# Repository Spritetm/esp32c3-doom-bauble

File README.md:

Doom on an ESP32-C3 based Christmas tree bauble
===============================================

This uses the GBA Doom from https://github.com/doomhack/GBADoom to put Doom on a tiny Christmas
bauble. More information is on https://spritesmods.com/?art=doom-bauble .

Directories
-----------

- case: contains OpenSCAD case designs. 
- esp32c3-doom: Contains the firmware. This needs ESP-IDF 5.0 or higher to compile.
- pcb - KiCad PCB designs

Case
----

You should be able to print the case on a FDM ('hot plastic squirter'-type) machine, 
but it'll look better when printed on a SLA/LCD/DLP ('ultra-violet goo hardener'-type)
printer. I masked it with masking tape afterwards and painted it with model paint
(specifically Tamiya TS-81 and TS-06 rattle-can paint).

PCB
---
The PCB designs and schematics are in Kicad format. Look at the schematics for hints 
for components not on the BOM. Note that the 'headers' on the PCB are supposed to have
wires directly soldered to it; space doesn't really allow for actual headers.

Firmware
--------

To build this, you need esp-idf 5.0 or higher. (I used git commit 4c1ff6016a, for reference.) You
also need to make sure you have 8MiB or more flash on your ESP32C3. You can use the standard 
esp-idf building & flashing procedure ('idf.py flash'). Note that you also need to flash the Doom
WAD to the flash. The flash-doom-wad.sh shellscript gives an example on how to do that with the
included doom1gba.wad file; using this will give you the shareware version of Doom (which includes
all the levels of Episode 1).

It is possible to use a different Doom WAD as a basis for this, but you need to manually convert 
it first. Tools and information for that is in the esp32c3-doom/GbaWadUtil. Most importantly, you
probably want to convert any music to IMF format and re-record demos before running GbaWadUtil
to generate the final WAD to be flashed.

Note that this Doom version is not compatible with demos that are included in existing WAD files; 
while they will play, they will likely desync early on. As such, you may want to re-record the
demo files. There's a rudimentary setup for this in esp32c3-doom/main/sdl which can be used to
compile this version of Doom for SDL input and output. After that, you can edit d_main.c and
recompile to enable demo recording of one map.

Note on input devices
---------------------

The ESP32C3 will connect to any BT-LE device that supports HID and is set to pairing mode. 
BT Classic devices aren't supported nor detected. Do note that connecting to an input 
device is not fast. Wait about 10 seconds after putting a device into pairing mode before 
using it.

Joystick has been tested and seems to work OK (although the input is digital only, no analog
movement is supported)

Mouse works, but again: inputs get flattened to digital-only. You may need a mouse 
with >=3 buttons to start the game (mouse wheel press / middle button = start)

Keyboard is implemented but entirely untested. The keymapping should be: z and x for 
shoot & open, a and s for left and right strafe, tab for select, enter for start, cursor 
keys for movement.

In general: weapon selection is hold open + use the strafe keys.

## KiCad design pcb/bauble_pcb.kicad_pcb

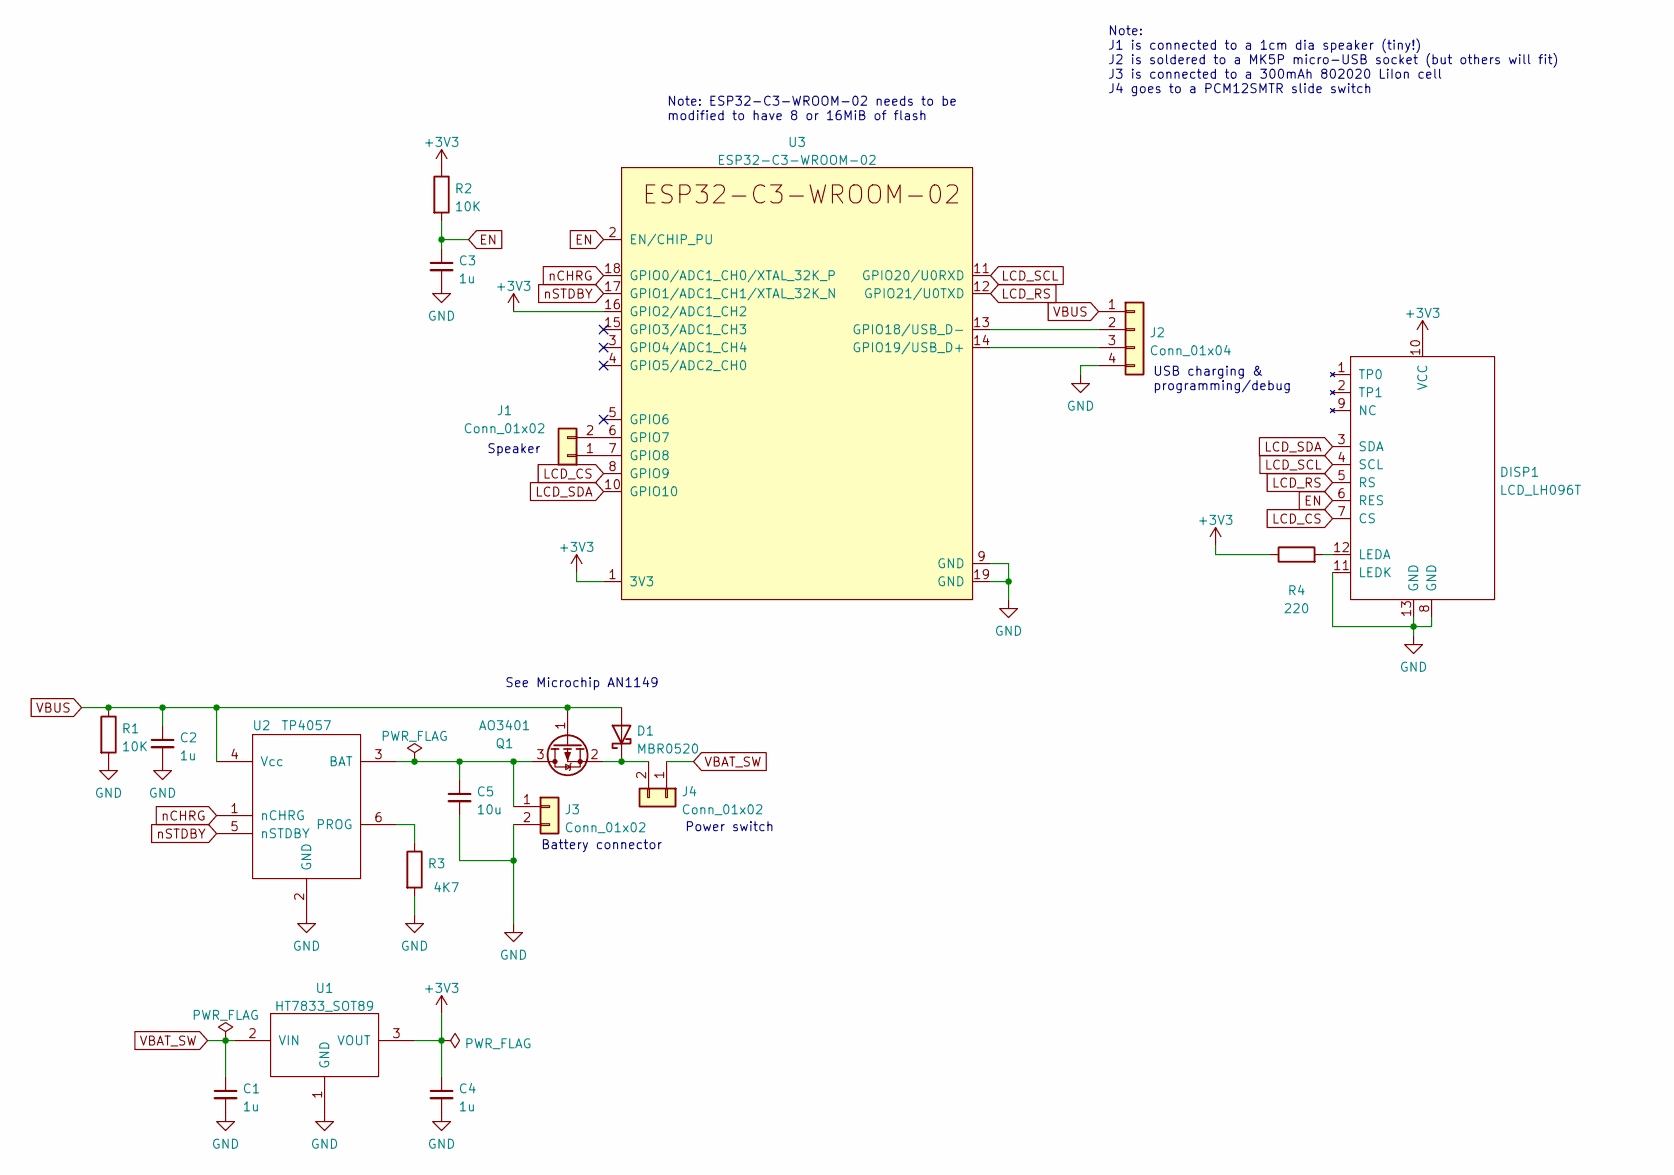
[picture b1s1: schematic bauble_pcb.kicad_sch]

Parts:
C1, C2, C3, C4: 1u; C_0603_1608Metric
C5: 10u; C_0805_2012Metric
D1: MBR0520; D_SOD-123
DISP1: LCD_LH096T; LCD_LH086T
J1, J3, J4: Conn_01x02; PinHeader_1x02_P1.27mm_Vertical
J2: Conn_01x04; PinHeader_1x04_P1.27mm_Vertical
Q1: AO3401; SOT-23
R1, R2: 10K; R_0603_1608Metric
R3: 4K7; R_0603_1608Metric
R4: 220; R_0603_1608Metric
U1: HT7833_SOT89; SOT-89-3
U2: TP4057; SOT-23-6
U3: ESP32-C3-WROOM-02

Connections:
+3V3: C4.1, DISP1.10 (VCC), R2.1, R4.1, U1.3 (VOUT), U3.1 (3V3), U3.16 (GPIO2/ADC1_CH2)
EN: C3.1, DISP1.6 (RES), R2.2, U3.2 (EN/CHIP_PU)
GND: C1.2, C2.2, C3.2, C4.2, C5.2, DISP1.8 (GND), DISP1.11 (LEDK), DISP1.13 (GND), J2.4, J3.2, R1.2, R3.2, U1.1 (GND), U2.2 (GND), U3.9 (GND), U3.19 (GND)
LCD_CS: DISP1.7 (CS), U3.8 (GPIO9)
LCD_RS: DISP1.5 (RS), U3.12 (GPIO21/U0TXD)
LCD_SCL: DISP1.4 (SCL), U3.11 (GPIO20/U0RXD)
LCD_SDA: DISP1.3 (SDA), U3.10 (GPIO10)
unnamed: C5.1, J3.1, Q1.3 (D), U2.3 (BAT)
unnamed: D1.1 (K), J4.2, Q1.2 (S)
unnamed: DISP1.12 (LEDA), R4.2
unnamed: J2.2, U3.13 (GPIO18/USB_D-)
unnamed: J2.3, U3.14 (GPIO19/USB_D+)
unnamed: R3.1, U2.6 (PROG)
unnamed: J1.2, U3.6 (GPIO7)
unnamed: J1.1, U3.7 (GPIO8)
VBAT_SW: C1.1, J4.1, U1.2 (VIN)
VBUS: C2.1, D1.2 (A), J2.1, Q1.1 (G), R1.1, U2.4 (Vcc)
nCHRG: U2.1 (nCHRG), U3.18 (GPIO0/ADC1_CH0/XTAL_32K_P)
nSTDBY: U2.5 (nSTDBY), U3.17 (GPIO1/ADC1_CH1/XTAL_32K_N)

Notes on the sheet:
See Microchip AN1149
Battery connector
Speaker
Note: ESP32-C3-WROOM-02 needs to be modified to have 8 or 16MiB of flash
Power switch
USB charging & programming/debug
Note: J1 is connected to a 1cm dia speaker (tiny!) J2 is soldered to a MK5P micro-USB socket (but others will fit) J3 is connected to a 300mAh 802020 LiIon cell J4 goes to a PCM12SMTR slide switch

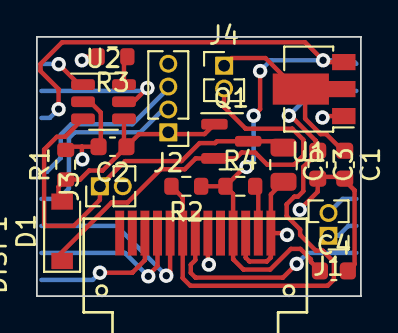
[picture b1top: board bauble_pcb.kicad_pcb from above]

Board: 2 copper layers, 18.0 x 14.4 mm, 19 parts (1 on the bottom side), 19 nets.

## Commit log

2021-07-03 Initial commit. Plays to serial console.
2021-07-04 Works on C3.
2021-07-04 Working audio
2021-07-04 Opl3 emulation... this one seems too slow.
2021-07-04 Change to DosBox OPL emu; change soundbank for generating imf files to original genmidi bank in wad
2022-11-13 omg bt input works kinda, needs some work
2022-11-15 Optimize memory usage
2022-11-15 Fix for audio volume, js
2022-11-15 Save memory...
2022-11-15 Save some more RAM, single-buffer the LCD. S1e2 now loads.
2022-11-20 Add sdl bindings
2022-11-21 Add demo recording back in; record some demos that do play back without desyncing; add infrastructure to add in those demos to doom1gba.wad
2022-12-04 Add other files; add preliminary support for mouse and keyboard
2022-12-05 Cleanup, add licenses to some files
